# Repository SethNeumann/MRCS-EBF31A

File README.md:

# REPO NAME: MRCS-EBF31A
## License: Creative Commons Attribution-NonCommercial-ShareAlike

The Electronic Battery Feed 31A provides power and off hook detection for a telephone talk circuit suitable for a Model Railroad dispatchers’ line. This is one of the circuits described in the New Operations SIG Book, A Compendium of Model Railroad Operations, Chapter 9.

EBF31A:

    Operates on 24 volts regulated DC, draws about 100 ma
    Supports at least 4 phones off hook at once, suitable for reading and copying orders on a TT&TO railroad
    Has a double-pole, double throw relay rated at 2A, with screw terminals for control of auxiliary circuits when off hook
    Has an LED "off hook" indicator
    Has an RJ11 jack and screw terminals for the phone line
    Has a 2.1mm center positive jack and screw terminals for power (supplies available from Jameco, Radio Shack, Amazon)
    Has a line level isolated monitor output on a stereo 3.5 mm audio jack
    snaps into the same 2.75" DIN rail that MRCS cpNodes and IOX16/32 expanders use

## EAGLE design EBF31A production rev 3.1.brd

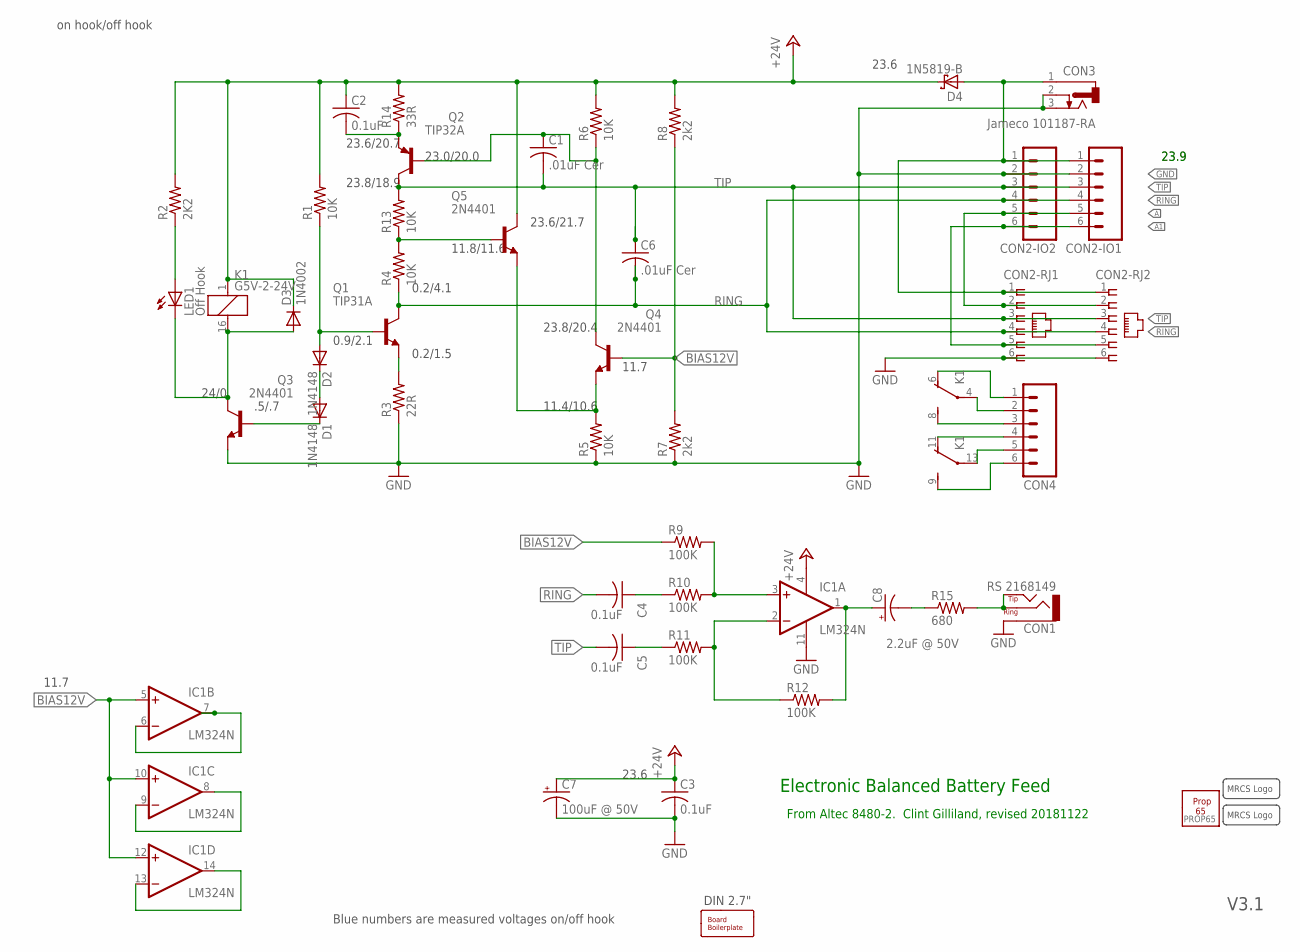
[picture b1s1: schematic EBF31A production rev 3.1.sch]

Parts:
C1, C6: .01uF Cer; C025-030X050
C2, C3, C4, C5: 0.1uF; C025-030X050
C7: 100uF @ 50V; E3,5-10
C8: 2.2uF @ 50V; E2-5
CON1: RS 2168149; AUDIO-JACK-3.5MM_STEREO
CON2-IO1, CON2-IO2, CON4: M06FEMALE_LOCK; 1X06_FEMALE_LOCK.010
CON2-RJ1, CON2-RJ2: CONNECTOR-RJ25-43860-2-MOLEX; RJ25-INVERTED
CON3: Jameco 101187-RA; DCJ0202
D1, D2: 1N4148; DIODE-1N4148
D3: 1N4002; DIODE-1N4148
D4: 1N5819-B; DO41-7.6
IC1: LM324N; DIL14
K1: G5V-2-24V; G5V-2
LED1: Off Hook; LED3MM
Q1: TIP31A; TO220
Q2: TIP32A; TO220
Q3, Q4, Q5: 2N4401; TO92-EBC
R1, R4, R5, R6, R13: 10K; AXIAL-0.4
R2: 2K2; AXIAL-0.4
R3: 22R; AXIAL-0.4
R7, R8: 2k2; AXIAL-0.4
R9, R10, R11, R12: 100K; AXIAL-0.4
R14: 33R; AXIAL-0.4
R15: 680; AXIAL-0.4
U$1: BOARD; BOARD-DINRAIL-2.71IN-MRCS
U$2, U$3: MRCS-LOGOBOT-LARGE; MRCS-LOGO
U$4: PROP65

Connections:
+24V: C2.1, C3.1, C7.+, D3.C, D4.C, IC1.4 (V+), K1.1, Q5.C, R1.P$2 (2), R2.P$2 (2), R6.P$2 (2), R8.P$2 (2), R14.P$2 (2)
A: CON2-IO1.5, CON2-IO2.5, CON2-RJ1.2, CON2-RJ2.2
A1: CON2-IO1.6, CON2-IO2.6, CON2-RJ1.5, CON2-RJ2.5
BIAS12V: IC1.5 (+IN), IC1.10 (+IN), IC1.12 (+IN), Q4.B, R7.P$2 (2), R8.P$1 (1), R9.P$1 (1)
GND: C3.2, C7.-, CON1.GND (SLEEVE), CON2-IO1.2, CON2-IO2.2, CON2-RJ1.6, CON2-RJ2.6, CON3.2, CON3.3, IC1.11 (V-), Q3.E, R3.P$1 (1), R5.P$1 (1), R7.P$1 (1)
unnamed: C2.2, Q2.3 (E), R14.P$1 (1)
unnamed: CON4.2, K1.4
unnamed: Q5.B, R4.P$2 (2), R13.P$1 (1)
unnamed: IC1.2 (-IN), R11.P$2 (2), R12.P$1 (1)
unnamed: Q1.3 (E), R3.P$2 (2)
unnamed: LED1.A, R2.P$1 (1)
unnamed: CON2-IO1.1, CON2-IO2.1, CON2-RJ1.1, CON2-RJ2.1, CON3.1, D4.A
unnamed: Q4.E, Q5.E, R5.P$2 (2)
unnamed: C1.1, Q2.1 (B), Q4.C, R6.P$1 (1)
unnamed: D1.C, Q3.B
unnamed: D1.A, D2.C
unnamed: D2.A, Q1.1 (B), R1.P$1 (1)
unnamed: D3.A, K1.16 (2), LED1.K (C), Q3.C
unnamed: IC1.13 (-IN), IC1.14 (OUT)
unnamed: CON4.6, K1.9 (S)
unnamed: CON4.1, K1.6 (O)
unnamed: CON4.3, K1.8 (S)
unnamed: C5.1, R11.P$1 (1)
unnamed: C8.+, IC1.1 (OUT), R12.P$2 (2)
unnamed: CON4.5, K1.13
unnamed: IC1.6 (-IN), IC1.7 (OUT)
unnamed: CON4.4, K1.11 (O)
unnamed: C8.-, R15.P$1 (1)
unnamed: CON1.RING, CON1.TIP, R15.P$2 (2)
unnamed: IC1.3 (+IN), R9.P$2 (2), R10.P$2 (2)
unnamed: C4.1, R10.P$1 (1)
unnamed: IC1.8 (OUT), IC1.9 (-IN)
RING: C4.2, C6.2, CON2-IO1.4, CON2-IO2.4, CON2-RJ1.4, CON2-RJ2.4, Q1.2 (C), R4.P$1 (1)
TIP: C1.2, C5.2, C6.1, CON2-IO1.3, CON2-IO2.3, CON2-RJ1.3, CON2-RJ2.3, Q2.2 (C), R13.P$2 (2)

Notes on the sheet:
Electronic Balanced Battery Feed
From Altec 8480-2. Clint Gilliland, revised 20181122
DIN 2.7"
V3.1
on hook/off hook
24/0
.5/.7
0.9/2.1
0.2/1.5
0.2/4.1
23.8/18.9
23.6/20.7
23.0/20.0
11.4/10.6
23.8/20.4
11.8/11.6
23.6/21.7
23.9
23.6
Blue numbers are measured voltages on/off hook
11.7

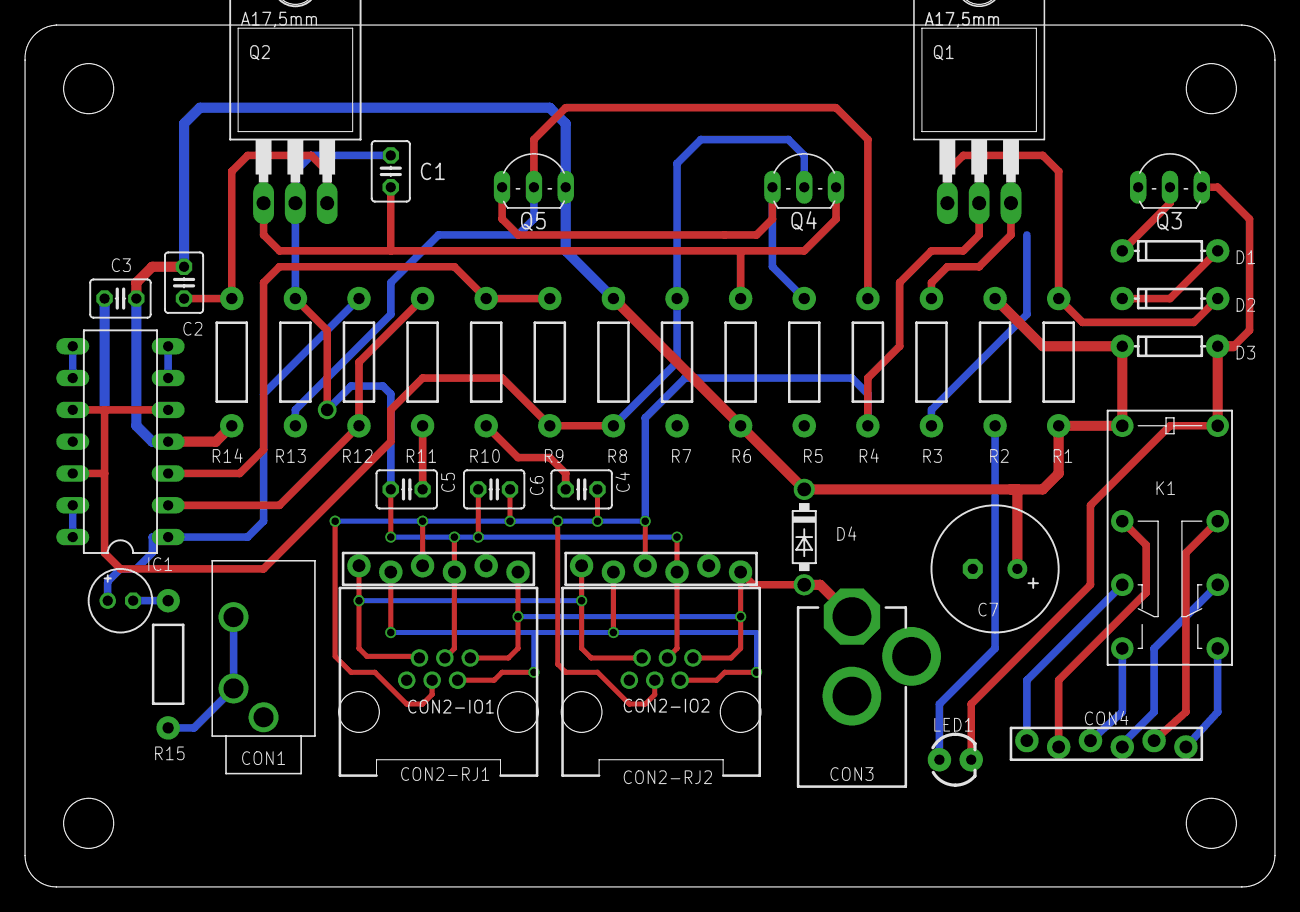
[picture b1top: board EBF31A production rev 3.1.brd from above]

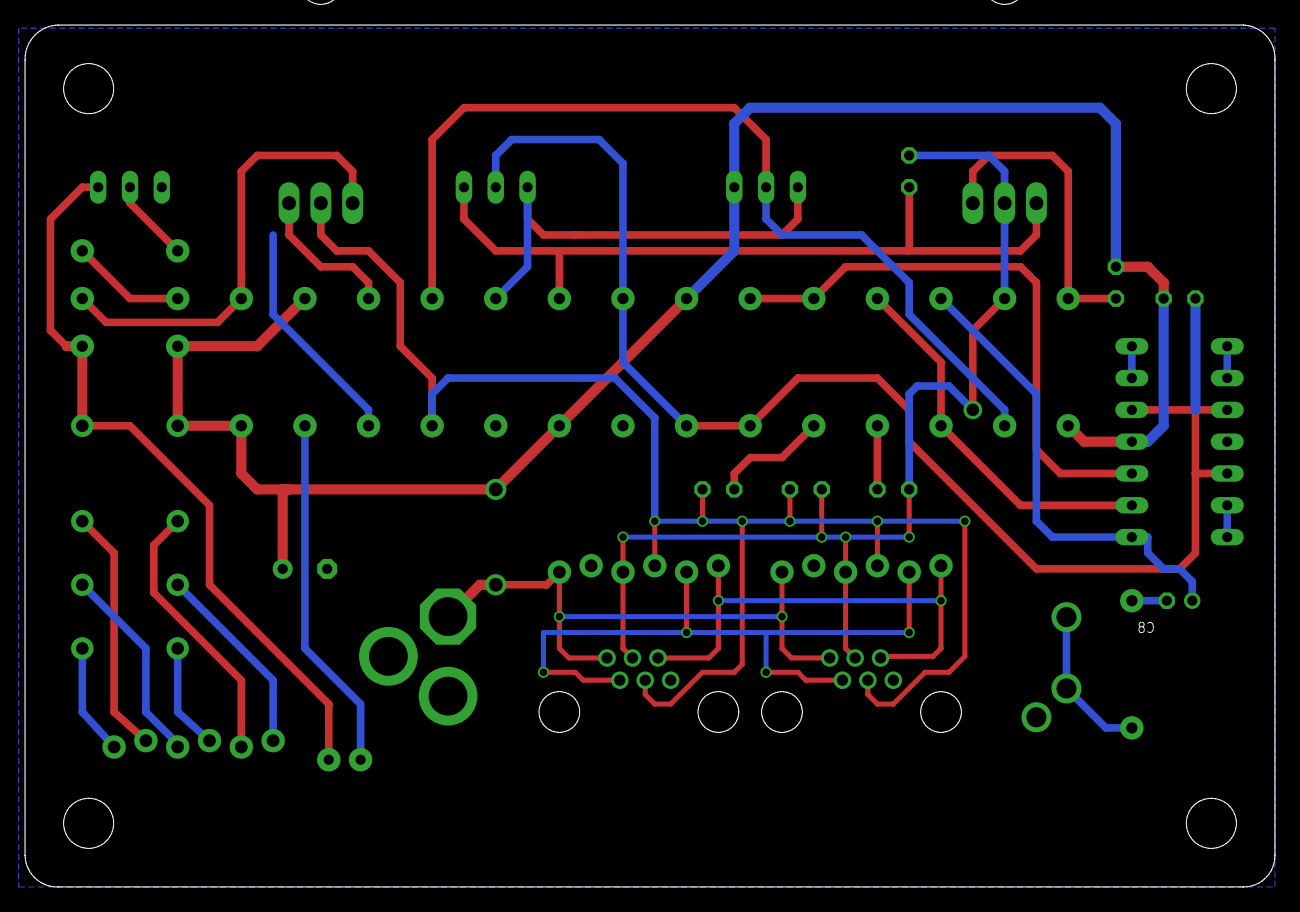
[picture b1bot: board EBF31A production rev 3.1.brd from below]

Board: 2 copper layers, 99.8 x 68.8 mm, 46 parts (2 on the bottom side), 34 nets.

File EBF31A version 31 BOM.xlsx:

Qty | Value | Device | Package | Parts | Description | Jameco | Digikey | Futurlec | Banggood/eBay | J$ | D$ | F$ | B$ | J Extd | D extd | F Extd | B Extd
1 |  | CONNECTOR-RJ25-43860-2-MOLEX | RJ25-INVERTED | CON2-RJ1, CON2-RJ2 | AMP connector |  | WM-5431-ND |  |  |  | 0.86 |  |  | 0 | 0.86 | 0 | 0
2 |  | M06FEMALE_LOCK | 1X06_FEMALE_LOCK.010 | CON2-IO1, CON2-IO2, CON4 | Header 6 |  |  |  | E-Salon | 0.6 |  |  |  | 1.2 | 0 | 0 | 0
1 | .01uF Cer | C-US025-030X050 | C025-030X050 | C1, DO NOT STUFF C6 | CAPACITOR, American symbol | 25507 |  |  |  | 0.19 |  |  |  | 0.19 | 0 | 0 | 0
4 | 0.1uF | C-US025-030X050 | C025-030X050 | C2, C3, C4, C5 | CAPACITOR, American symbol | 25523 |  |  |  | 0.19 |  |  |  | 0.76 | 0 | 0 | 0
4 | 100K | RESISTORPTH-1/4W | AXIAL-0.4 | R9, R10, R11, R12 | Resistor | 691340 |  |  |  | 0.02 |  |  |  | 0.08 | 0 | 0 | 0
1 | 100uF @ 50V | CPOL-USE3.5-10 | E3,5-10 | C7 | POLARIZED CAPACITOR, American symbol | 29962 |  |  |  | 0.1 |  |  |  | 0.1 | 0 | 0 | 0
5 | 10K | RESISTORPTH-1/4W | AXIAL-0.4 | R1, R4, R5, R6, R13 | Resistor | 691104 |  |  |  | 0.02 |  |  |  | 0.1 | 0 | 0 | 0
1 | 1N4002 | DIODE1N4001 | DIODE-1N4148 | D3 | Diode | 35975 |  |  |  | 0.05 |  |  |  | 0.05 | 0 | 0 | 0
2 | 1N4148 | DIODE1N4148 | DIODE-1N4148 | D1, D2 | Diode | 36038 |  |  |  | 0.04 |  |  |  | 0.08 | 0 | 0 | 0
1 | 1N5819-B | 1N5819-B | DO41-7.6 | D4 | 1.0A SCHOTTKY BARRIER RECTIFIER | 177965 |  |  |  | 0.19 |  |  |  | 0.19 | 0 | 0 | 0
1 | 2.2uF @ 50V | CPOL-USE2-5 | E2-5 | C8 | POLARIZED CAPACITOR, American symbol | 93731 |  |  |  | 0.09 |  |  |  | 0.09 | 0 | 0 | 0
1 | 22R | RESISTORPTH-1/4W | AXIAL-0.4 | R3 | Resistor | 690460 |  |  |  | 0.02 |  |  |  | 0.02 | 0 | 0 | 0
3 | 2K2 | RESISTORPTH-1/4W | AXIAL-0.4 | R2, R7, R8 | Resistor | 690945 |  |  |  | 0.02 |  |  |  | 0.06 | 0 | 0 | 0
3 | 2N4401 | 2N4401/2N3904 | TO92-EBC | Q3, Q4, Q5 | NPN Transistror | 783498 |  |  |  | 0.05 |  |  |  | 0.15000000000000002 | 0 | 0 | 0
1 | 33R | RESISTORPTH-1/4W | AXIAL-0.4 | R14 | Resistor | 690507 |  |  |  | 0.02 |  |  |  | 0.02 | 0 | 0 | 0
1 | 680 | RESISTORPTH-1/4W | AXIAL-0.4 | R15 | Resistor | 690822 |  |  |  | 0.02 |  |  |  | 0.02 | 0 | 0 | 0
1 | BOARD | BOARD69X100MRCS | BOARD-DINRAIL-2.71IN-MRCS | U$1 |  |  |  |  | Seeed |  |  |  | 1.03 | 0 | 0 | 0 | 1.03
1 | G5V-2-24V | G5V-2 | G5V-2 | K1 | OMRON PCB Relay |  |  |  |  |  |  | 1.1200000000000001 |  | 0 | 0 | 1.1200000000000001 | 0
1 | Jameco 101187-RA | CONNECTOR-DC-POWER-RA | DCJ0202 | CON3 | DC POWER JACK | 101187 |  |  |  | 0.69 |  |  |  | 0.69 | 0 | 0 | 0
1 | LM324N | LM324N | DIL14 | IC1 | OP AMP | 23683 |  |  |  | 0.17 |  |  |  | 0.17 | 0 | 0 | 0
1 | Off Hook | LED3MM | LED3MM | LED1 | LEDs |  |  |  | kits |  |  |  | 0.01 | 0 | 0 | 0 | 0.01
1 | RS 2168149 | CONNECTOR-AUDIO3.5MM-ADAMTECH | AUDIO-JACK-3.5MM_STEREO | CON1 | 3.5mm Audio Jack | 2168149 |  |  |  | 0.99 |  |  |  | 0.99 | 0 | 0 | 0
1 | TIP31A | TIP31C | TO220 | Q1 | NPN Transistor | 33048 |  |  |  | 0.35 |  |  |  | 0.35 | 0 | 0 | 0
1 | TIP32A | TIP32C | TO220 | Q2 | PNP Transistor | 181841 |  |  |  | 0.35 |  |  |  | 0.35 | 0 | 0 | 0
1 |  | 14 pin DIP Socket | 14 pin DIP | IC1S | 14 pin DIP Socket | 112214 |  |  |  | 0.11 |  |  |  | 0.11 | 0 | 0 | 0
 |  |  |  |  |  |  |  |  |  |  |  |  |  | 5.77 | 0.86 | 1.1200000000000001 | 1.04 | 8.7899999999999991
 |  |  |  |  |  |  |  |  |  |  |  |  |  |  |  |  | 0.2 | 1.758
 |  |  |  |  |  |  |  |  |  |  |  |  |  |  | Parts subtotal |  |  | 10.547999999999998
 |  |  |  |  |  |  |  |  |  |  |  |  |  |  | Labor |  |  | 23.85
 |  |  |  |  |  |  |  |  |  |  |  |  |  |  |  |  | 0.2 | 4.7700000000000005
 |  |  |  |  |  |  |  |  |  |  |  |  |  |  | Labor Subtotal |  |  | 28.62
 |  |  |  |  |  |  |  |  |  |  |  |  |  |  | Parts and Labor |  |  | 39.167999999999999
 |  |  |  |  |  |  |  |  |  |  |  |  |  |  | e-Commerce |  | 0.1 | 3.9168000000000003
 |  |  |  |  |  |  |  |  |  |  |  |  |  |  | Grand Total |  |  | 43.084800000000001

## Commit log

2021-03-08 intial commit
    migrated existing project in at version 3.1
2021-03-08 initial commit
    migrated existing product into repository
2021-03-08 initial commit
    same old
2021-03-08 intial commit
2021-03-08 initial commit
    migrated existing product
2021-03-08 initial migration to GitHub
    Eagle files and BOM

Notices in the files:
parts and their libraries:
SparkFun-DiscreteSemi: Licensing: CC v3.0 Share-Alike You are welcome to use this library for commercial purposes.
